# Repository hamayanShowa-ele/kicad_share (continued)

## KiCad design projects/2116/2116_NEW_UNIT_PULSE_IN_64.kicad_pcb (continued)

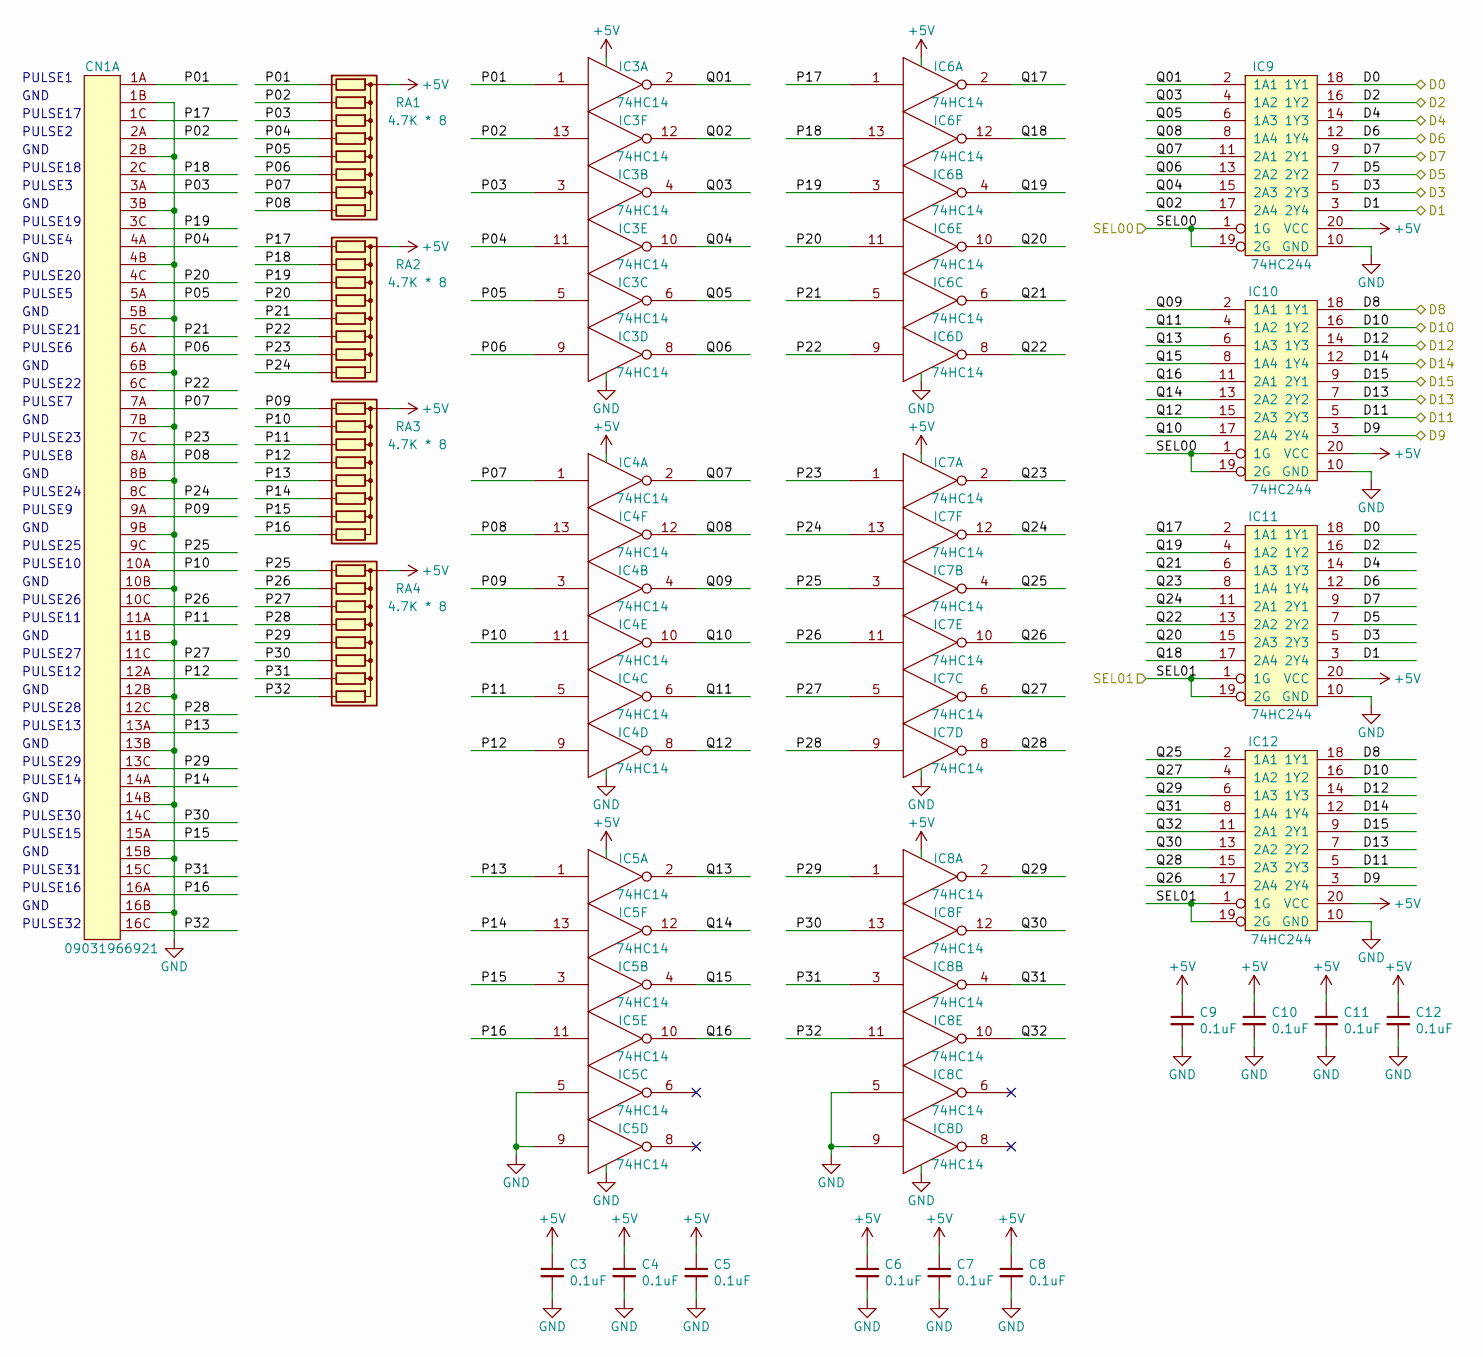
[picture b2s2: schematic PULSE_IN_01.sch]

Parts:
C3, C4, C5, C6, C7, C8, C9, C10, C11, C12: 0.1uF; C_0603
CN1: 09031966921; cn_09031966921
IC3, IC4, IC5, IC6, IC7, IC8: 74HC14; IC_DIP-14_W7.62mm
IC9, IC10, IC11, IC12: 74HC244; ic_DIP-20_W7.62mm
RA1, RA2, RA3, RA4: 4.7K * 8; RKC1_8B8

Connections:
+5V: C3.1, C4.1, C5.1, C6.1, C7.1, C8.1, C9.1, C10.1, C11.1, C12.1, IC3.14 (+5V), IC4.14 (+5V), IC5.14 (+5V), IC6.14 (+5V), IC7.14 (+5V), IC8.14 (+5V), IC9.20 (VCC), IC10.20 (VCC), IC11.20 (VCC), IC12.20 (VCC), RA1.1 (common), RA2.1 (common), RA3.1 (common), RA4.1 (common); also elsewhere on the board
/D0: IC9.18 (1Y1), IC11.18 (1Y1); also elsewhere on the board
/D1: IC9.3 (2Y4), IC11.3 (2Y4); also elsewhere on the board
/D2: IC9.16 (1Y2), IC11.16 (1Y2); also elsewhere on the board
/D3: IC9.5 (2Y3), IC11.5 (2Y3); also elsewhere on the board
/D4: IC9.14 (1Y3), IC11.14 (1Y3); also elsewhere on the board
/D5: IC9.7 (2Y2), IC11.7 (2Y2); also elsewhere on the board
/D6: IC9.12 (1Y4), IC11.12 (1Y4); also elsewhere on the board
/D7: IC9.9 (2Y1), IC11.9 (2Y1); also elsewhere on the board
/D8: IC10.18 (1Y1), IC12.18 (1Y1); also elsewhere on the board
/D9: IC10.3 (2Y4), IC12.3 (2Y4); also elsewhere on the board
/D10: IC10.16 (1Y2), IC12.16 (1Y2); also elsewhere on the board
/D11: IC10.5 (2Y3), IC12.5 (2Y3); also elsewhere on the board
/D12: IC10.14 (1Y3), IC12.14 (1Y3); also elsewhere on the board
/D13: IC10.7 (2Y2), IC12.7 (2Y2); also elsewhere on the board
/D14: IC10.12 (1Y4), IC12.12 (1Y4); also elsewhere on the board
/D15: IC10.9 (2Y1), IC12.9 (2Y1); also elsewhere on the board
/PULSE_IN_01/P01: CN1.1A, IC3.1, RA1.2 (R1)
/PULSE_IN_01/P02: CN1.2A, IC3.13, RA1.3 (R2)
/PULSE_IN_01/P03: CN1.3A, IC3.3, RA1.4 (R3)
/PULSE_IN_01/P04: CN1.4A, IC3.11, RA1.5 (R4)
/PULSE_IN_01/P05: CN1.5A, IC3.5, RA1.6 (R5)
/PULSE_IN_01/P06: CN1.6A, IC3.9, RA1.7 (R6)
/PULSE_IN_01/P07: CN1.7A, IC4.1, RA1.8 (R7)
/PULSE_IN_01/P08: CN1.8A, IC4.13, RA1.9 (R8)
/PULSE_IN_01/P09: CN1.9A, IC4.3, RA3.2 (R1)
/PULSE_IN_01/P10: CN1.10A, IC4.11, RA3.3 (R2)
/PULSE_IN_01/P11: CN1.11A, IC4.5, RA3.4 (R3)
/PULSE_IN_01/P12: CN1.12A, IC4.9, RA3.5 (R4)
/PULSE_IN_01/P13: CN1.13A, IC5.1, RA3.6 (R5)
/PULSE_IN_01/P14: CN1.14A, IC5.13, RA3.7 (R6)
/PULSE_IN_01/P15: CN1.15A, IC5.3, RA3.8 (R7)
/PULSE_IN_01/P16: CN1.16A, IC5.11, RA3.9 (R8)
/PULSE_IN_01/P17: CN1.1C, IC6.1, RA2.2 (R1)
/PULSE_IN_01/P18: CN1.2C, IC6.13, RA2.3 (R2)
/PULSE_IN_01/P19: CN1.3C, IC6.3, RA2.4 (R3)
/PULSE_IN_01/P20: CN1.4C, IC6.11, RA2.5 (R4)
/PULSE_IN_01/P21: CN1.5C, IC6.5, RA2.6 (R5)
/PULSE_IN_01/P22: CN1.6C, IC6.9, RA2.7 (R6)
/PULSE_IN_01/P23: CN1.7C, IC7.1, RA2.8 (R7)
/PULSE_IN_01/P24: CN1.8C, IC7.13, RA2.9 (R8)
/PULSE_IN_01/P25: CN1.9C, IC7.3, RA4.2 (R1)
/PULSE_IN_01/P26: CN1.10C, IC7.11, RA4.3 (R2)
/PULSE_IN_01/P27: CN1.11C, IC7.5, RA4.4 (R3)
/PULSE_IN_01/P28: CN1.12C, IC7.9, RA4.5 (R4)
/PULSE_IN_01/P29: CN1.13C, IC8.1, RA4.6 (R5)
/PULSE_IN_01/P30: CN1.14C, IC8.13, RA4.7 (R6)
/PULSE_IN_01/P31: CN1.15C, IC8.3, RA4.8 (R7)
/PULSE_IN_01/P32: CN1.16C, IC8.11, RA4.9 (R8)
/PULSE_IN_01/Q01: IC3.2, IC9.2 (1A1)
/PULSE_IN_01/Q02: IC3.12, IC9.17 (2A4)
/PULSE_IN_01/Q03: IC3.4, IC9.4 (1A2)
/PULSE_IN_01/Q04: IC3.10, IC9.15 (2A3)
/PULSE_IN_01/Q05: IC3.6, IC9.6 (1A3)
/PULSE_IN_01/Q06: IC3.8, IC9.13 (2A2)
/PULSE_IN_01/Q07: IC4.2, IC9.11 (2A1)
/PULSE_IN_01/Q08: IC4.12, IC9.8 (1A4)
/PULSE_IN_01/Q09: IC4.4, IC10.2 (1A1)
/PULSE_IN_01/Q10: IC4.10, IC10.17 (2A4)
/PULSE_IN_01/Q11: IC4.6, IC10.4 (1A2)
/PULSE_IN_01/Q12: IC4.8, IC10.15 (2A3)
/PULSE_IN_01/Q13: IC5.2, IC10.6 (1A3)
/PULSE_IN_01/Q14: IC5.12, IC10.13 (2A2)
/PULSE_IN_01/Q15: IC5.4, IC10.8 (1A4)
/PULSE_IN_01/Q16: IC5.10, IC10.11 (2A1)
/PULSE_IN_01/Q17: IC6.2, IC11.2 (1A1)
/PULSE_IN_01/Q18: IC6.12, IC11.17 (2A4)
/PULSE_IN_01/Q19: IC6.4, IC11.4 (1A2)
/PULSE_IN_01/Q20: IC6.10, IC11.15 (2A3)
/PULSE_IN_01/Q21: IC6.6, IC11.6 (1A3)
/PULSE_IN_01/Q22: IC6.8, IC11.13 (2A2)
/PULSE_IN_01/Q23: IC7.2, IC11.8 (1A4)
/PULSE_IN_01/Q24: IC7.12, IC11.11 (2A1)
/PULSE_IN_01/Q25: IC7.4, IC12.2 (1A1)
/PULSE_IN_01/Q26: IC7.10, IC12.17 (2A4)
/PULSE_IN_01/Q27: IC7.6, IC12.4 (1A2)
/PULSE_IN_01/Q28: IC7.8, IC12.15 (2A3)
/PULSE_IN_01/Q29: IC8.2, IC12.6 (1A3)
/PULSE_IN_01/Q30: IC8.12, IC12.13 (2A2)
/PULSE_IN_01/Q31: IC8.4, IC12.8 (1A4)
/PULSE_IN_01/Q32: IC8.10, IC12.11 (2A1)
/SEL00: IC9.1 (1G), IC9.19 (2G), IC10.1 (1G), IC10.19 (2G); also elsewhere on the board
/SEL01: IC11.1 (1G), IC11.19 (2G), IC12.1 (1G), IC12.19 (2G); also elsewhere on the board
GND: C3.2, C4.2, C5.2, C6.2, C7.2, C8.2, C9.2, C10.2, C11.2, C12.2, CN1.1B, CN1.2B, CN1.3B, CN1.4B, CN1.5B, CN1.6B, CN1.7B, CN1.8B, CN1.9B, CN1.10B, CN1.11B, CN1.12B, CN1.13B, CN1.14B, CN1.15B, CN1.16B, IC3.7 (GND), IC4.7 (GND), IC5.5, IC5.7 (GND), IC5.9, IC6.7 (GND), IC7.7 (GND), IC8.5, IC8.7 (GND), IC8.9, IC9.10 (GND), IC10.10 (GND), IC11.10 (GND), IC12.10 (GND); also elsewhere on the board

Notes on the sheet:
GND
PULSE1
PULSE2
PULSE3
PULSE4
PULSE5
PULSE6
PULSE7
PULSE8
PULSE9
PULSE10
PULSE11
PULSE12
PULSE13
PULSE14
PULSE15
PULSE16
PULSE32
PULSE17
PULSE18
PULSE19
PULSE20
PULSE21
PULSE22
PULSE23
PULSE24
PULSE25
PULSE26
PULSE27
PULSE28
PULSE29
PULSE30
PULSE31

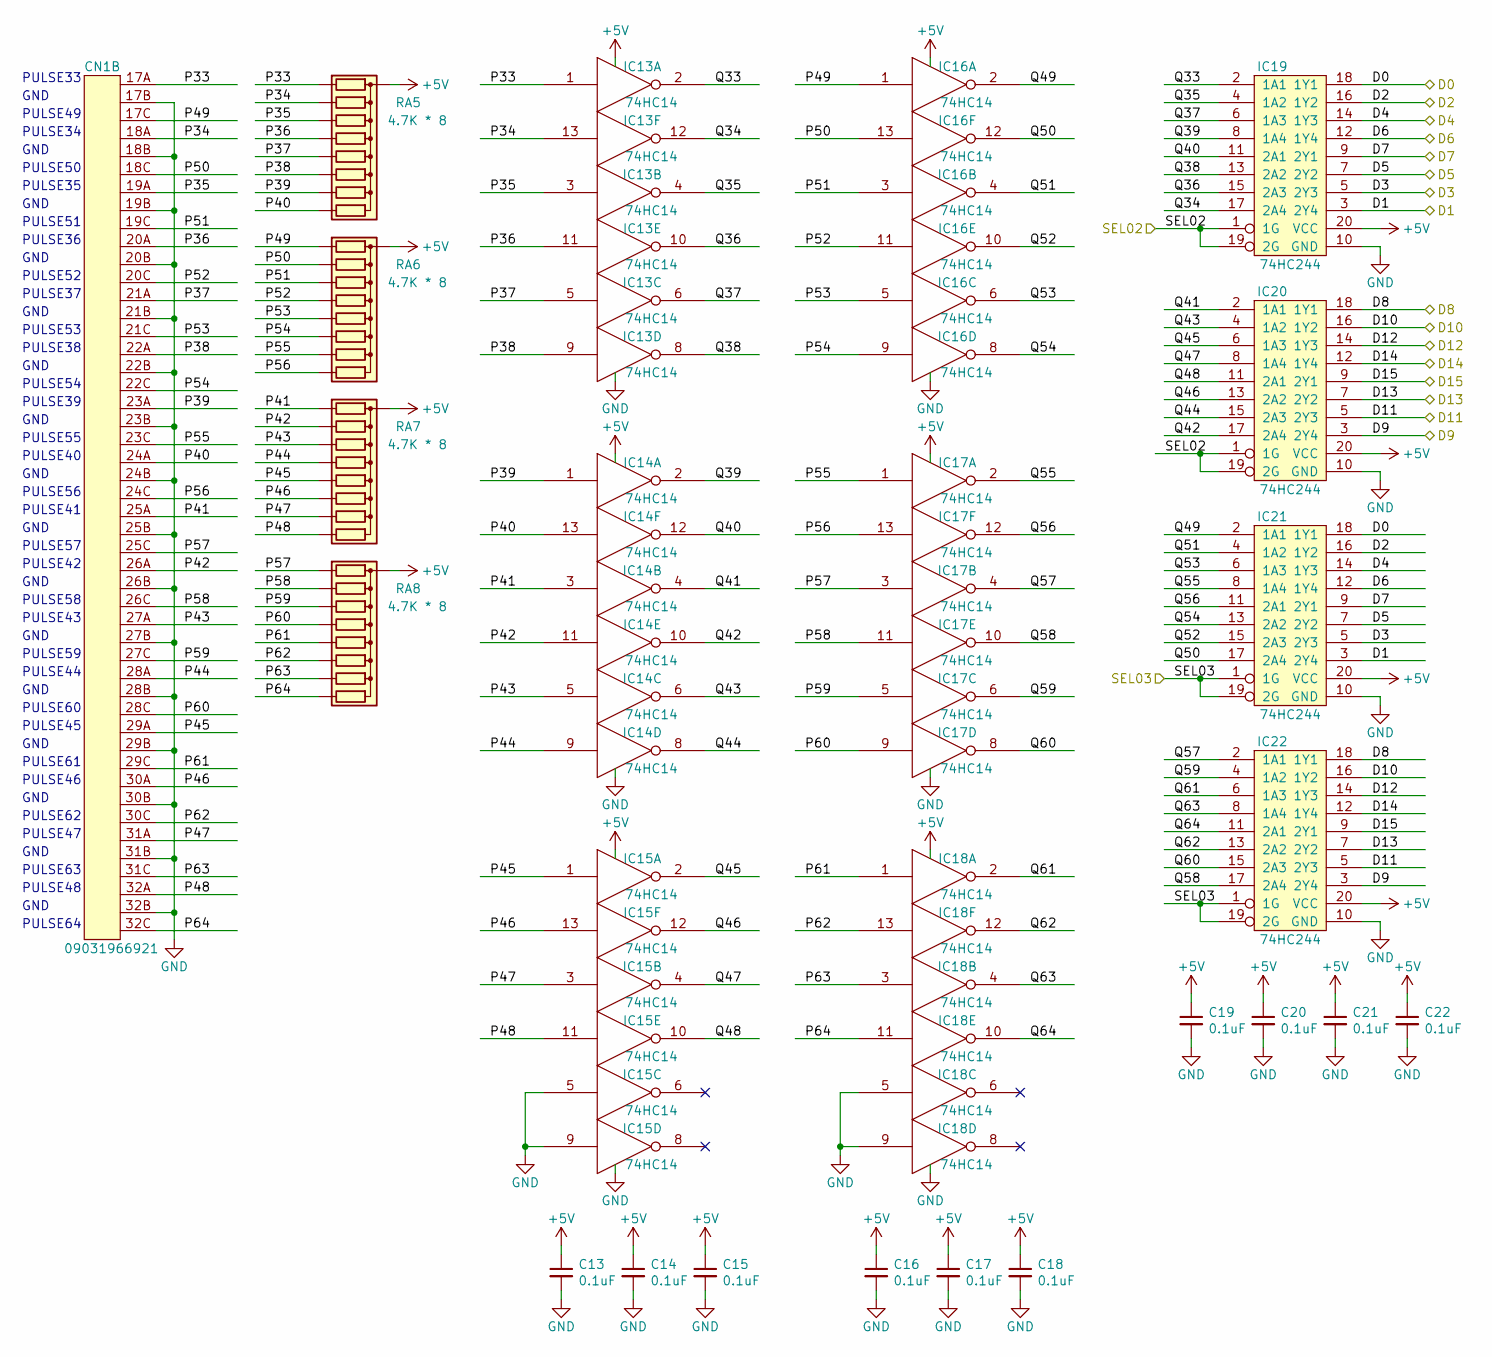
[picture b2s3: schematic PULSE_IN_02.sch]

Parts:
C13, C14, C15, C16, C17, C18, C19, C20, C21, C22: 0.1uF; C_0603
CN1: 09031966921; cn_09031966921
IC13, IC14, IC15, IC16, IC17, IC18: 74HC14; IC_DIP-14_W7.62mm
IC19, IC20, IC21, IC22: 74HC244; ic_DIP-20_W7.62mm
RA5, RA6, RA7, RA8: 4.7K * 8; RKC1_8B8

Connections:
+5V: C13.1, C14.1, C15.1, C16.1, C17.1, C18.1, C19.1, C20.1, C21.1, C22.1, IC13.14 (+5V), IC14.14 (+5V), IC15.14 (+5V), IC16.14 (+5V), IC17.14 (+5V), IC18.14 (+5V), IC19.20 (VCC), IC20.20 (VCC), IC21.20 (VCC), IC22.20 (VCC), RA5.1 (common), RA6.1 (common), RA7.1 (common), RA8.1 (common); also elsewhere on the board
/D0: IC19.18 (1Y1), IC21.18 (1Y1); also elsewhere on the board
/D1: IC19.3 (2Y4), IC21.3 (2Y4); also elsewhere on the board
/D2: IC19.16 (1Y2), IC21.16 (1Y2); also elsewhere on the board
/D3: IC19.5 (2Y3), IC21.5 (2Y3); also elsewhere on the board
/D4: IC19.14 (1Y3), IC21.14 (1Y3); also elsewhere on the board
/D5: IC19.7 (2Y2), IC21.7 (2Y2); also elsewhere on the board
/D6: IC19.12 (1Y4), IC21.12 (1Y4); also elsewhere on the board
/D7: IC19.9 (2Y1), IC21.9 (2Y1); also elsewhere on the board
/D8: IC20.18 (1Y1), IC22.18 (1Y1); also elsewhere on the board
/D9: IC20.3 (2Y4), IC22.3 (2Y4); also elsewhere on the board
/D10: IC20.16 (1Y2), IC22.16 (1Y2); also elsewhere on the board
/D11: IC20.5 (2Y3), IC22.5 (2Y3); also elsewhere on the board
/D12: IC20.14 (1Y3), IC22.14 (1Y3); also elsewhere on the board
/D13: IC20.7 (2Y2), IC22.7 (2Y2); also elsewhere on the board
/D14: IC20.12 (1Y4), IC22.12 (1Y4); also elsewhere on the board
/D15: IC20.9 (2Y1), IC22.9 (2Y1); also elsewhere on the board
/PULSE_IN_02/P33: CN1.17A, IC13.1, RA5.2 (R1)
/PULSE_IN_02/P34: CN1.18A, IC13.13, RA5.3 (R2)
/PULSE_IN_02/P35: CN1.19A, IC13.3, RA5.4 (R3)
/PULSE_IN_02/P36: CN1.20A, IC13.11, RA5.5 (R4)
/PULSE_IN_02/P37: CN1.21A, IC13.5, RA5.6 (R5)
/PULSE_IN_02/P38: CN1.22A, IC13.9, RA5.7 (R6)
/PULSE_IN_02/P39: CN1.23A, IC14.1, RA5.8 (R7)
/PULSE_IN_02/P40: CN1.24A, IC14.13, RA5.9 (R8)
/PULSE_IN_02/P41: CN1.25A, IC14.3, RA7.2 (R1)
/PULSE_IN_02/P42: CN1.26A, IC14.11, RA7.3 (R2)
/PULSE_IN_02/P43: CN1.27A, IC14.5, RA7.4 (R3)
/PULSE_IN_02/P44: CN1.28A, IC14.9, RA7.5 (R4)
/PULSE_IN_02/P45: CN1.29A, IC15.1, RA7.6 (R5)
/PULSE_IN_02/P46: CN1.30A, IC15.13, RA7.7 (R6)
/PULSE_IN_02/P47: CN1.31A, IC15.3, RA7.8 (R7)
/PULSE_IN_02/P48: CN1.32A, IC15.11, RA7.9 (R8)
/PULSE_IN_02/P49: CN1.17C, IC16.1, RA6.2 (R1)
/PULSE_IN_02/P50: CN1.18C, IC16.13, RA6.3 (R2)
/PULSE_IN_02/P51: CN1.19C, IC16.3, RA6.4 (R3)
/PULSE_IN_02/P52: CN1.20C, IC16.11, RA6.5 (R4)
/PULSE_IN_02/P53: CN1.21C, IC16.5, RA6.6 (R5)
/PULSE_IN_02/P54: CN1.22C, IC16.9, RA6.7 (R6)
/PULSE_IN_02/P55: CN1.23C, IC17.1, RA6.8 (R7)
/PULSE_IN_02/P56: CN1.24C, IC17.13, RA6.9 (R8)
/PULSE_IN_02/P57: CN1.25C, IC17.3, RA8.2 (R1)
/PULSE_IN_02/P58: CN1.26C, IC17.11, RA8.3 (R2)
/PULSE_IN_02/P59: CN1.27C, IC17.5, RA8.4 (R3)
/PULSE_IN_02/P60: CN1.28C, IC17.9, RA8.5 (R4)
/PULSE_IN_02/P61: CN1.29C, IC18.1, RA8.6 (R5)
/PULSE_IN_02/P62: CN1.30C, IC18.13, RA8.7 (R6)
/PULSE_IN_02/P63: CN1.31C, IC18.3, RA8.8 (R7)
/PULSE_IN_02/P64: CN1.32C, IC18.11, RA8.9 (R8)
/PULSE_IN_02/Q33: IC13.2, IC19.2 (1A1)
/PULSE_IN_02/Q34: IC13.12, IC19.17 (2A4)
/PULSE_IN_02/Q35: IC13.4, IC19.4 (1A2)
/PULSE_IN_02/Q36: IC13.10, IC19.15 (2A3)
/PULSE_IN_02/Q37: IC13.6, IC19.6 (1A3)
/PULSE_IN_02/Q38: IC13.8, IC19.13 (2A2)
/PULSE_IN_02/Q39: IC14.2, IC19.8 (1A4)
/PULSE_IN_02/Q40: IC14.12, IC19.11 (2A1)
/PULSE_IN_02/Q41: IC14.4, IC20.2 (1A1)
/PULSE_IN_02/Q42: IC14.10, IC20.17 (2A4)
/PULSE_IN_02/Q43: IC14.6, IC20.4 (1A2)
/PULSE_IN_02/Q44: IC14.8, IC20.15 (2A3)
/PULSE_IN_02/Q45: IC15.2, IC20.6 (1A3)
/PULSE_IN_02/Q46: IC15.12, IC20.13 (2A2)
/PULSE_IN_02/Q47: IC15.4, IC20.8 (1A4)
/PULSE_IN_02/Q48: IC15.10, IC20.11 (2A1)
/PULSE_IN_02/Q49: IC16.2, IC21.2 (1A1)
/PULSE_IN_02/Q50: IC16.12, IC21.17 (2A4)
/PULSE_IN_02/Q51: IC16.4, IC21.4 (1A2)
/PULSE_IN_02/Q52: IC16.10, IC21.15 (2A3)
/PULSE_IN_02/Q53: IC16.6, IC21.6 (1A3)
/PULSE_IN_02/Q54: IC16.8, IC21.13 (2A2)
/PULSE_IN_02/Q55: IC17.2, IC21.8 (1A4)
/PULSE_IN_02/Q56: IC17.12, IC21.11 (2A1)
/PULSE_IN_02/Q57: IC17.4, IC22.2 (1A1)
/PULSE_IN_02/Q58: IC17.10, IC22.17 (2A4)
/PULSE_IN_02/Q59: IC17.6, IC22.4 (1A2)
/PULSE_IN_02/Q60: IC17.8, IC22.15 (2A3)
/PULSE_IN_02/Q61: IC18.2, IC22.6 (1A3)
/PULSE_IN_02/Q62: IC18.12, IC22.13 (2A2)
/PULSE_IN_02/Q63: IC18.4, IC22.8 (1A4)
/PULSE_IN_02/Q64: IC18.10, IC22.11 (2A1)
/SEL02: IC19.1 (1G), IC19.19 (2G), IC20.1 (1G), IC20.19 (2G); also elsewhere on the board
/SEL03: IC21.1 (1G), IC21.19 (2G), IC22.1 (1G), IC22.19 (2G); also elsewhere on the board
GND: C13.2, C14.2, C15.2, C16.2, C17.2, C18.2, C19.2, C20.2, C21.2, C22.2, CN1.17B, CN1.18B, CN1.19B, CN1.20B, CN1.21B, CN1.22B, CN1.23B, CN1.24B, CN1.25B, CN1.26B, CN1.27B, CN1.28B, CN1.29B, CN1.30B, CN1.31B, CN1.32B, IC13.7 (GND), IC14.7 (GND), IC15.5, IC15.7 (GND), IC15.9, IC16.7 (GND), IC17.7 (GND), IC18.5, IC18.7 (GND), IC18.9, IC19.10 (GND), IC20.10 (GND), IC21.10 (GND), IC22.10 (GND); also elsewhere on the board

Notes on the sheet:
PULSE33
PULSE34
PULSE36
PULSE37
PULSE38
PULSE39
PULSE40
PULSE41
PULSE42
PULSE43
PULSE44
PULSE45
PULSE46
PULSE47
PULSE48
GND
PULSE64
PULSE49
PULSE50
PULSE51
PULSE52
PULSE53
PULSE54
PULSE55
PULSE56
PULSE57
PULSE58
PULSE59
PULSE60
PULSE61
PULSE62
PULSE63
PULSE35

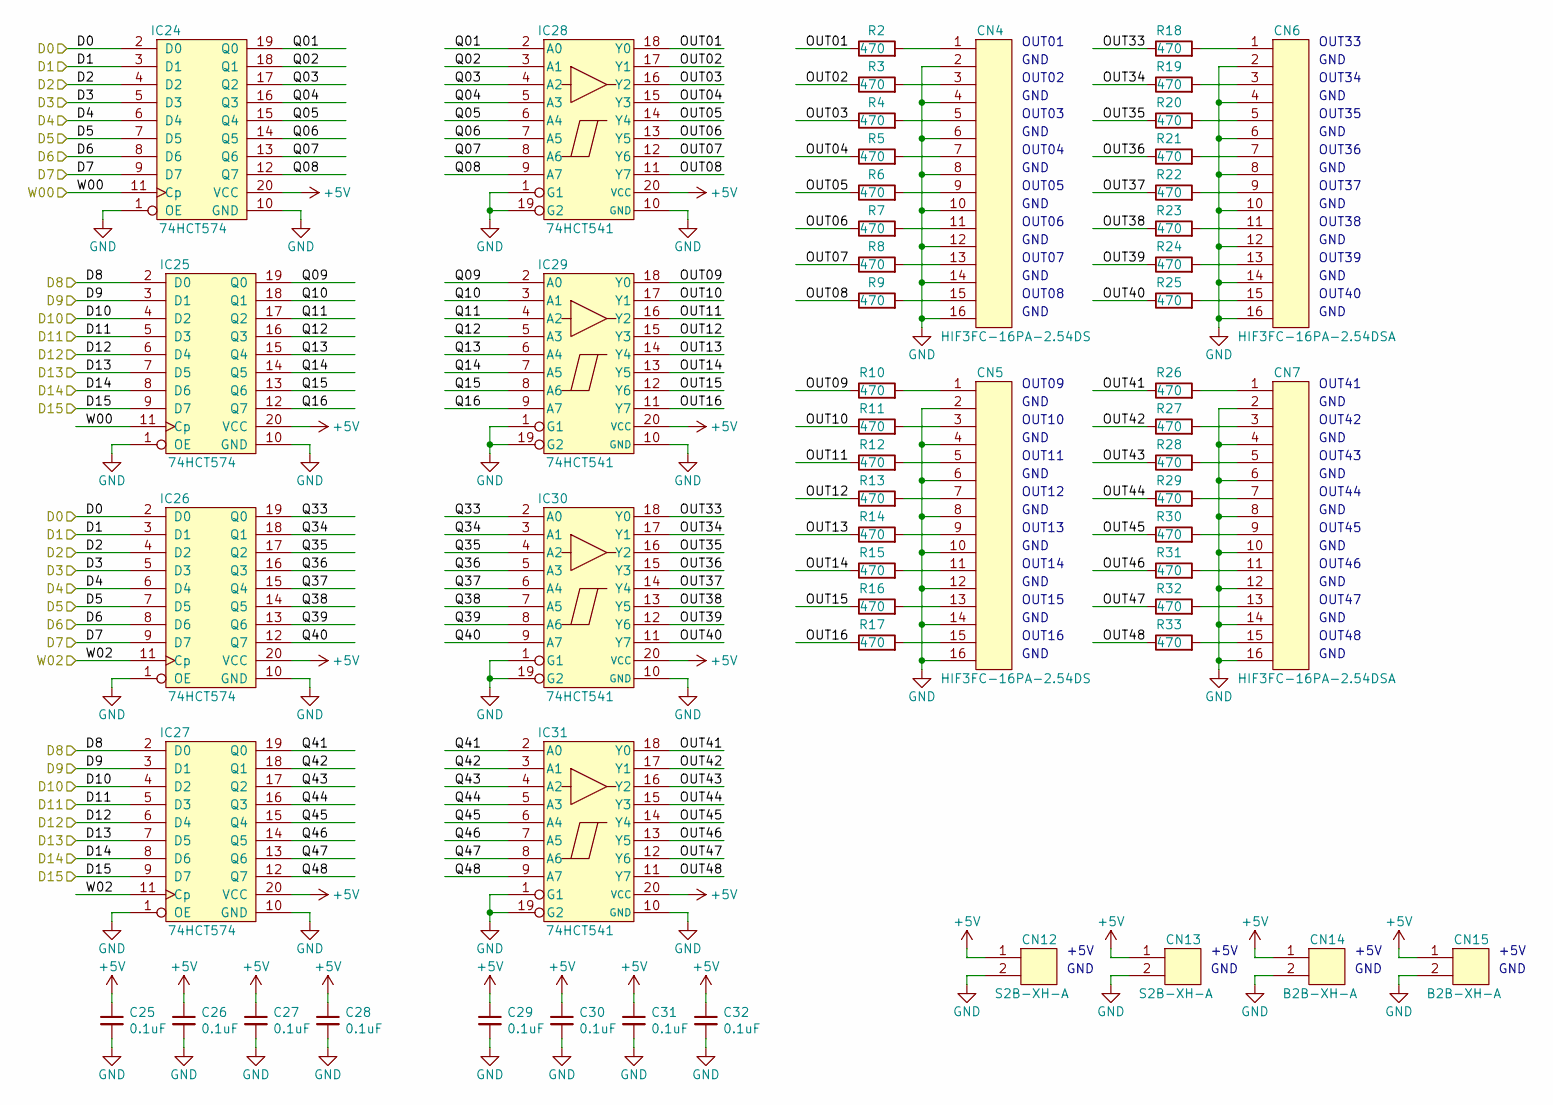
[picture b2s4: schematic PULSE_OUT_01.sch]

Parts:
C25, C26, C27, C28, C29, C30, C31, C32: 0.1uF; C_0603
CN4, CN5: HIF3FC-16PA-2.54DS; cn_HIF3FC-16PA-254DS
CN6, CN7: HIF3FC-16PA-2.54DSA; cn_HIF3FC-16PA-254DSA
CN12, CN13: S2B-XH-A
CN14, CN15: B2B-XH-A; cn_B2B-XH-A
IC24, IC25, IC26, IC27: 74HCT574; ic_DIP-20_W7.62mm
IC28, IC29, IC30, IC31: 74HCT541; ic_DIP-20_W7.62mm
R2, R3, R4, R5, R6, R7, R8, R9, R10, R11, R12, R13, R14, R15, R16, R17, R18, R19, R20, R21, R22, R23, R24, R25, R26, R27, R28, R29, R30, R31, R32, R33: 470; C_0603

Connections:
+5V: C25.1, C26.1, C27.1, C28.1, C29.1, C30.1, C31.1, C32.1, CN12.1, CN13.1, CN14.1, CN15.1, IC24.20 (VCC), IC25.20 (VCC), IC26.20 (VCC), IC27.20 (VCC), IC28.20 (VCC), IC29.20 (VCC), IC30.20 (VCC), IC31.20 (VCC); also elsewhere on the board
/D0: IC24.2 (D0), IC26.2 (D0); also elsewhere on the board
/D1: IC24.3 (D1), IC26.3 (D1); also elsewhere on the board
/D2: IC24.4 (D2), IC26.4 (D2); also elsewhere on the board
/D3: IC24.5 (D3), IC26.5 (D3); also elsewhere on the board
/D4: IC24.6 (D4), IC26.6 (D4); also elsewhere on the board
/D5: IC24.7 (D5), IC26.7 (D5); also elsewhere on the board
/D6: IC24.8 (D6), IC26.8 (D6); also elsewhere on the board
/D7: IC24.9 (D7), IC26.9 (D7); also elsewhere on the board
/D8: IC25.2 (D0), IC27.2 (D0); also elsewhere on the board
/D9: IC25.3 (D1), IC27.3 (D1); also elsewhere on the board
/D10: IC25.4 (D2), IC27.4 (D2); also elsewhere on the board
/D11: IC25.5 (D3), IC27.5 (D3); also elsewhere on the board
/D12: IC25.6 (D4), IC27.6 (D4); also elsewhere on the board
/D13: IC25.7 (D5), IC27.7 (D5); also elsewhere on the board
/D14: IC25.8 (D6), IC27.8 (D6); also elsewhere on the board
/D15: IC25.9 (D7), IC27.9 (D7); also elsewhere on the board
/PULSE_OUT_01/OUT01: IC28.18 (Y0), R2.1
/PULSE_OUT_01/OUT02: IC28.17 (Y1), R3.1
/PULSE_OUT_01/OUT03: IC28.16 (Y2), R4.1
/PULSE_OUT_01/OUT04: IC28.15 (Y3), R5.1
/PULSE_OUT_01/OUT05: IC28.14 (Y4), R6.1
/PULSE_OUT_01/OUT06: IC28.13 (Y5), R7.1
/PULSE_OUT_01/OUT07: IC28.12 (Y6), R8.1
/PULSE_OUT_01/OUT08: IC28.11 (Y7), R9.1
/PULSE_OUT_01/OUT09: IC29.18 (Y0), R10.1
/PULSE_OUT_01/OUT10: IC29.17 (Y1), R11.1
/PULSE_OUT_01/OUT11: IC29.16 (Y2), R12.1
/PULSE_OUT_01/OUT12: IC29.15 (Y3), R13.1
/PULSE_OUT_01/OUT13: IC29.14 (Y4), R14.1
/PULSE_OUT_01/OUT14: IC29.13 (Y5), R15.1
/PULSE_OUT_01/OUT15: IC29.12 (Y6), R16.1
/PULSE_OUT_01/OUT16: IC29.11 (Y7), R17.1
/PULSE_OUT_01/OUT33: IC30.18 (Y0), R18.1
/PULSE_OUT_01/OUT34: IC30.17 (Y1), R19.1
/PULSE_OUT_01/OUT35: IC30.16 (Y2), R20.1
/PULSE_OUT_01/OUT36: IC30.15 (Y3), R21.1
/PULSE_OUT_01/OUT37: IC30.14 (Y4), R22.1
/PULSE_OUT_01/OUT38: IC30.13 (Y5), R23.1
/PULSE_OUT_01/OUT39: IC30.12 (Y6), R24.1
/PULSE_OUT_01/OUT40: IC30.11 (Y7), R25.1
/PULSE_OUT_01/OUT41: IC31.18 (Y0), R26.1
/PULSE_OUT_01/OUT42: IC31.17 (Y1), R27.1
/PULSE_OUT_01/OUT43: IC31.16 (Y2), R28.1
/PULSE_OUT_01/OUT44: IC31.15 (Y3), R29.1
/PULSE_OUT_01/OUT45: IC31.14 (Y4), R30.1
/PULSE_OUT_01/OUT46: IC31.13 (Y5), R31.1
/PULSE_OUT_01/OUT47: IC31.12 (Y6), R32.1
/PULSE_OUT_01/OUT48: IC31.11 (Y7), R33.1
/PULSE_OUT_01/Q01: IC24.19 (Q0), IC28.2 (A0)
/PULSE_OUT_01/Q02: IC24.18 (Q1), IC28.3 (A1)
/PULSE_OUT_01/Q03: IC24.17 (Q2), IC28.4 (A2)
/PULSE_OUT_01/Q04: IC24.16 (Q3), IC28.5 (A3)
/PULSE_OUT_01/Q05: IC24.15 (Q4), IC28.6 (A4)
/PULSE_OUT_01/Q06: IC24.14 (Q5), IC28.7 (A5)
/PULSE_OUT_01/Q07: IC24.13 (Q6), IC28.8 (A6)
/PULSE_OUT_01/Q08: IC24.12 (Q7), IC28.9 (A7)
/PULSE_OUT_01/Q09: IC25.19 (Q0), IC29.2 (A0)
/PULSE_OUT_01/Q10: IC25.18 (Q1), IC29.3 (A1)
/PULSE_OUT_01/Q11: IC25.17 (Q2), IC29.4 (A2)
/PULSE_OUT_01/Q12: IC25.16 (Q3), IC29.5 (A3)
/PULSE_OUT_01/Q13: IC25.15 (Q4), IC29.6 (A4)
/PULSE_OUT_01/Q14: IC25.14 (Q5), IC29.7 (A5)
/PULSE_OUT_01/Q15: IC25.13 (Q6), IC29.8 (A6)
/PULSE_OUT_01/Q16: IC25.12 (Q7), IC29.9 (A7)
/PULSE_OUT_01/Q33: IC26.19 (Q0), IC30.2 (A0)
/PULSE_OUT_01/Q34: IC26.18 (Q1), IC30.3 (A1)
/PULSE_OUT_01/Q35: IC26.17 (Q2), IC30.4 (A2)
/PULSE_OUT_01/Q36: IC26.16 (Q3), IC30.5 (A3)
/PULSE_OUT_01/Q37: IC26.15 (Q4), IC30.6 (A4)
/PULSE_OUT_01/Q38: IC26.14 (Q5), IC30.7 (A5)
/PULSE_OUT_01/Q39: IC26.13 (Q6), IC30.8 (A6)
/PULSE_OUT_01/Q40: IC26.12 (Q7), IC30.9 (A7)
/PULSE_OUT_01/Q41: IC27.19 (Q0), IC31.2 (A0)
/PULSE_OUT_01/Q42: IC27.18 (Q1), IC31.3 (A1)
/PULSE_OUT_01/Q43: IC27.17 (Q2), IC31.4 (A2)
/PULSE_OUT_01/Q44: IC27.16 (Q3), IC31.5 (A3)
/PULSE_OUT_01/Q45: IC27.15 (Q4), IC31.6 (A4)
/PULSE_OUT_01/Q46: IC27.14 (Q5), IC31.7 (A5)
/PULSE_OUT_01/Q47: IC27.13 (Q6), IC31.8 (A6)
/PULSE_OUT_01/Q48: IC27.12 (Q7), IC31.9 (A7)
/W00: IC24.11 (Cp), IC25.11 (Cp); also elsewhere on the board
/W02: IC26.11 (Cp), IC27.11 (Cp); also elsewhere on the board
GND: C25.2, C26.2, C27.2, C28.2, C29.2, C30.2, C31.2, C32.2, CN4.2, CN4.4, CN4.6, CN4.8, CN4.10, CN4.12, CN4.14, CN4.16, CN5.2, CN5.4, CN5.6, CN5.8, CN5.10, CN5.12, CN5.14, CN5.16, CN6.2, CN6.4, CN6.6, CN6.8, CN6.10, CN6.12, CN6.14, CN6.16, CN7.2, CN7.4, CN7.6, CN7.8, CN7.10, CN7.12, CN7.14, CN7.16, CN12.2, CN13.2, CN14.2, CN15.2, IC24.1 (OE), IC24.10 (GND), IC25.1 (OE), IC25.10 (GND), IC26.1 (OE), IC26.10 (GND), IC27.1 (OE), IC27.10 (GND), IC28.1 (G1), IC28.10 (GND), IC28.19 (G2), IC29.1 (G1), IC29.10 (GND), IC29.19 (G2), IC30.1 (G1), IC30.10 (GND), IC30.19 (G2), IC31.1 (G1), IC31.10 (GND), IC31.19 (G2); also elsewhere on the board
unnamed: CN4.1, R2.2
unnamed: CN4.3, R3.2
unnamed: CN4.5, R4.2
unnamed: CN4.7, R5.2
unnamed: CN4.9, R6.2
unnamed: CN4.11, R7.2
unnamed: CN4.13, R8.2
unnamed: CN4.15, R9.2
unnamed: CN5.1, R10.2
unnamed: CN5.3, R11.2
unnamed: CN5.5, R12.2
unnamed: CN5.7, R13.2
unnamed: CN5.9, R14.2
unnamed: CN5.11, R15.2
unnamed: CN5.13, R16.2
unnamed: CN5.15, R17.2
unnamed: CN6.1, R18.2
unnamed: CN6.3, R19.2
unnamed: CN6.5, R20.2
unnamed: CN6.7, R21.2
unnamed: CN6.9, R22.2
unnamed: CN6.11, R23.2
unnamed: CN6.13, R24.2
unnamed: CN6.15, R25.2
unnamed: CN7.1, R26.2
unnamed: CN7.3, R27.2
unnamed: CN7.5, R28.2
unnamed: CN7.7, R29.2
unnamed: CN7.9, R30.2
unnamed: CN7.11, R31.2
unnamed: CN7.13, R32.2
unnamed: CN7.15, R33.2

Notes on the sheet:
OUT33
GND
OUT34
OUT35
OUT36
OUT37
OUT38
OUT39
OUT40
OUT41
OUT42
OUT43
OUT44
OUT45
OUT46
OUT47
OUT48
OUT01
OUT02
OUT03
OUT04
OUT05
OUT06
OUT07
OUT08
OUT09
OUT10
OUT11
OUT12
OUT13
OUT14
OUT15
OUT16
+5V

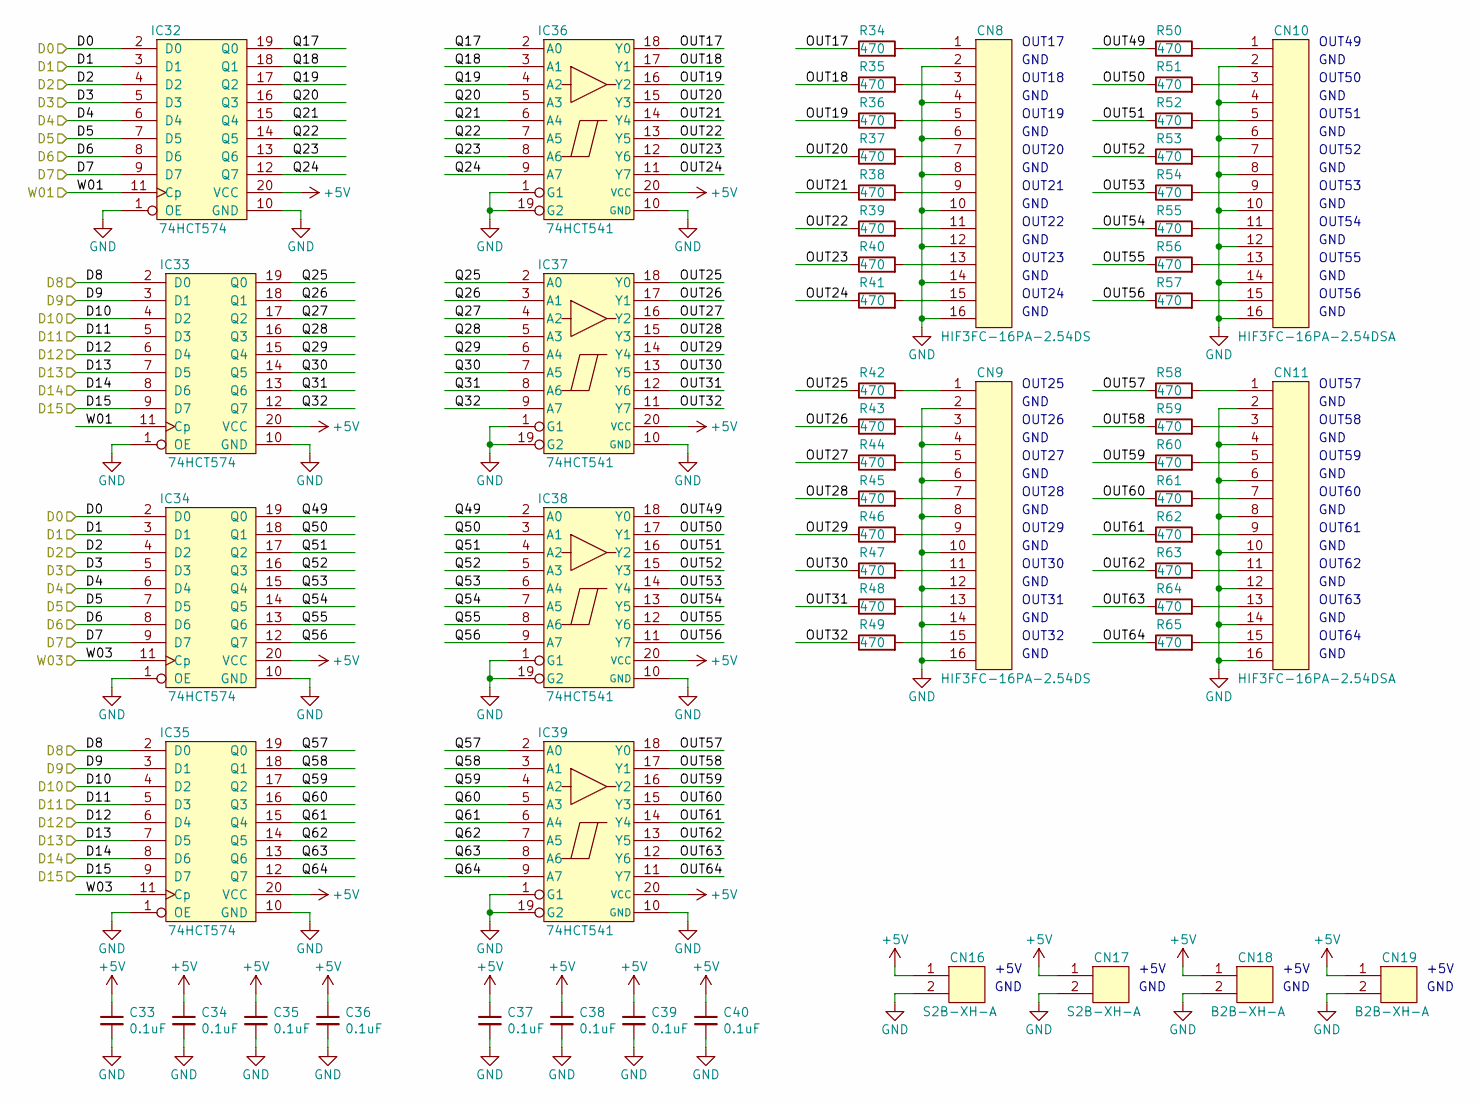
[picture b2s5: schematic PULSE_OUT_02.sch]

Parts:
C33, C34, C35, C36, C37, C38, C39, C40: 0.1uF; C_0603
CN8, CN9: HIF3FC-16PA-2.54DS; cn_HIF3FC-16PA-254DS
CN10, CN11: HIF3FC-16PA-2.54DSA; cn_HIF3FC-16PA-254DSA
CN16, CN17: S2B-XH-A
CN18, CN19: B2B-XH-A; cn_B2B-XH-A
IC32, IC33, IC34, IC35: 74HCT574; ic_DIP-20_W7.62mm
IC36, IC37, IC38, IC39: 74HCT541; ic_DIP-20_W7.62mm
R34, R35, R36, R37, R38, R39, R40, R41, R42, R43, R44, R45, R46, R47, R48, R49, R50, R51, R52, R53, R54, R55, R56, R57, R58, R59, R60, R61, R62, R63, R64, R65: 470; C_0603

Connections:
+5V: C33.1, C34.1, C35.1, C36.1, C37.1, C38.1, C39.1, C40.1, CN16.1, CN17.1, CN18.1, CN19.1, IC32.20 (VCC), IC33.20 (VCC), IC34.20 (VCC), IC35.20 (VCC), IC36.20 (VCC), IC37.20 (VCC), IC38.20 (VCC), IC39.20 (VCC); also elsewhere on the board
/D0: IC32.2 (D0), IC34.2 (D0); also elsewhere on the board
/D1: IC32.3 (D1), IC34.3 (D1); also elsewhere on the board
/D2: IC32.4 (D2), IC34.4 (D2); also elsewhere on the board
/D3: IC32.5 (D3), IC34.5 (D3); also elsewhere on the board
/D4: IC32.6 (D4), IC34.6 (D4); also elsewhere on the board
/D5: IC32.7 (D5), IC34.7 (D5); also elsewhere on the board
/D6: IC32.8 (D6), IC34.8 (D6); also elsewhere on the board
/D7: IC32.9 (D7), IC34.9 (D7); also elsewhere on the board
/D8: IC33.2 (D0), IC35.2 (D0); also elsewhere on the board
/D9: IC33.3 (D1), IC35.3 (D1); also elsewhere on the board
/D10: IC33.4 (D2), IC35.4 (D2); also elsewhere on the board
/D11: IC33.5 (D3), IC35.5 (D3); also elsewhere on the board
/D12: IC33.6 (D4), IC35.6 (D4); also elsewhere on the board
/D13: IC33.7 (D5), IC35.7 (D5); also elsewhere on the board
/D14: IC33.8 (D6), IC35.8 (D6); also elsewhere on the board
/D15: IC33.9 (D7), IC35.9 (D7); also elsewhere on the board
/PULSE_OUT_02/OUT17: IC36.18 (Y0), R34.1
/PULSE_OUT_02/OUT18: IC36.17 (Y1), R35.1
/PULSE_OUT_02/OUT19: IC36.16 (Y2), R36.1
/PULSE_OUT_02/OUT20: IC36.15 (Y3), R37.1
/PULSE_OUT_02/OUT21: IC36.14 (Y4), R38.1
/PULSE_OUT_02/OUT22: IC36.13 (Y5), R39.1
/PULSE_OUT_02/OUT23: IC36.12 (Y6), R40.1
/PULSE_OUT_02/OUT24: IC36.11 (Y7), R41.1
/PULSE_OUT_02/OUT25: IC37.18 (Y0), R42.1
/PULSE_OUT_02/OUT26: IC37.17 (Y1), R43.1
/PULSE_OUT_02/OUT27: IC37.16 (Y2), R44.1
/PULSE_OUT_02/OUT28: IC37.15 (Y3), R45.1
/PULSE_OUT_02/OUT29: IC37.14 (Y4), R46.1
/PULSE_OUT_02/OUT30: IC37.13 (Y5), R47.1
/PULSE_OUT_02/OUT31: IC37.12 (Y6), R48.1
/PULSE_OUT_02/OUT32: IC37.11 (Y7), R49.1
/PULSE_OUT_02/OUT49: IC38.18 (Y0), R50.1
/PULSE_OUT_02/OUT50: IC38.17 (Y1), R51.1
/PULSE_OUT_02/OUT51: IC38.16 (Y2), R52.1
/PULSE_OUT_02/OUT52: IC38.15 (Y3), R53.1
/PULSE_OUT_02/OUT53: IC38.14 (Y4), R54.1
/PULSE_OUT_02/OUT54: IC38.13 (Y5), R55.1
/PULSE_OUT_02/OUT55: IC38.12 (Y6), R56.1
/PULSE_OUT_02/OUT56: IC38.11 (Y7), R57.1
/PULSE_OUT_02/OUT57: IC39.18 (Y0), R58.1
/PULSE_OUT_02/OUT58: IC39.17 (Y1), R59.1
/PULSE_OUT_02/OUT59: IC39.16 (Y2), R60.1
/PULSE_OUT_02/OUT60: IC39.15 (Y3), R61.1
/PULSE_OUT_02/OUT61: IC39.14 (Y4), R62.1
/PULSE_OUT_02/OUT62: IC39.13 (Y5), R63.1
/PULSE_OUT_02/OUT63: IC39.12 (Y6), R64.1
/PULSE_OUT_02/OUT64: IC39.11 (Y7), R65.1
/PULSE_OUT_02/Q17: IC32.19 (Q0), IC36.2 (A0)
/PULSE_OUT_02/Q18: IC32.18 (Q1), IC36.3 (A1)
/PULSE_OUT_02/Q19: IC32.17 (Q2), IC36.4 (A2)
/PULSE_OUT_02/Q20: IC32.16 (Q3), IC36.5 (A3)
/PULSE_OUT_02/Q21: IC32.15 (Q4), IC36.6 (A4)
/PULSE_OUT_02/Q22: IC32.14 (Q5), IC36.7 (A5)
/PULSE_OUT_02/Q23: IC32.13 (Q6), IC36.8 (A6)
/PULSE_OUT_02/Q24: IC32.12 (Q7), IC36.9 (A7)
/PULSE_OUT_02/Q25: IC33.19 (Q0), IC37.2 (A0)
/PULSE_OUT_02/Q26: IC33.18 (Q1), IC37.3 (A1)
/PULSE_OUT_02/Q27: IC33.17 (Q2), IC37.4 (A2)
/PULSE_OUT_02/Q28: IC33.16 (Q3), IC37.5 (A3)
/PULSE_OUT_02/Q29: IC33.15 (Q4), IC37.6 (A4)
/PULSE_OUT_02/Q30: IC33.14 (Q5), IC37.7 (A5)
/PULSE_OUT_02/Q31: IC33.13 (Q6), IC37.8 (A6)
/PULSE_OUT_02/Q32: IC33.12 (Q7), IC37.9 (A7)
/PULSE_OUT_02/Q49: IC34.19 (Q0), IC38.2 (A0)
/PULSE_OUT_02/Q50: IC34.18 (Q1), IC38.3 (A1)
/PULSE_OUT_02/Q51: IC34.17 (Q2), IC38.4 (A2)
/PULSE_OUT_02/Q52: IC34.16 (Q3), IC38.5 (A3)
/PULSE_OUT_02/Q53: IC34.15 (Q4), IC38.6 (A4)
/PULSE_OUT_02/Q54: IC34.14 (Q5), IC38.7 (A5)
/PULSE_OUT_02/Q55: IC34.13 (Q6), IC38.8 (A6)
/PULSE_OUT_02/Q56: IC34.12 (Q7), IC38.9 (A7)
/PULSE_OUT_02/Q57: IC35.19 (Q0), IC39.2 (A0)
/PULSE_OUT_02/Q58: IC35.18 (Q1), IC39.3 (A1)
/PULSE_OUT_02/Q59: IC35.17 (Q2), IC39.4 (A2)
/PULSE_OUT_02/Q60: IC35.16 (Q3), IC39.5 (A3)
/PULSE_OUT_02/Q61: IC35.15 (Q4), IC39.6 (A4)
/PULSE_OUT_02/Q62: IC35.14 (Q5), IC39.7 (A5)
/PULSE_OUT_02/Q63: IC35.13 (Q6), IC39.8 (A6)
/PULSE_OUT_02/Q64: IC35.12 (Q7), IC39.9 (A7)
/W01: IC32.11 (Cp), IC33.11 (Cp); also elsewhere on the board
/W03: IC34.11 (Cp), IC35.11 (Cp); also elsewhere on the board
GND: C33.2, C34.2, C35.2, C36.2, C37.2, C38.2, C39.2, C40.2, CN8.2, CN8.4, CN8.6, CN8.8, CN8.10, CN8.12, CN8.14, CN8.16, CN9.2, CN9.4, CN9.6, CN9.8, CN9.10, CN9.12, CN9.14, CN9.16, CN10.2, CN10.4, CN10.6, CN10.8, CN10.10, CN10.12, CN10.14, CN10.16, CN11.2, CN11.4, CN11.6, CN11.8, CN11.10, CN11.12, CN11.14, CN11.16, CN16.2, CN17.2, CN18.2, CN19.2, IC32.1 (OE), IC32.10 (GND), IC33.1 (OE), IC33.10 (GND), IC34.1 (OE), IC34.10 (GND), IC35.1 (OE), IC35.10 (GND), IC36.1 (G1), IC36.10 (GND), IC36.19 (G2), IC37.1 (G1), IC37.10 (GND), IC37.19 (G2), IC38.1 (G1), IC38.10 (GND), IC38.19 (G2), IC39.1 (G1), IC39.10 (GND), IC39.19 (G2); also elsewhere on the board
unnamed: CN8.1, R34.2
unnamed: CN8.3, R35.2
unnamed: CN8.5, R36.2
unnamed: CN8.7, R37.2
unnamed: CN8.9, R38.2
unnamed: CN8.11, R39.2
unnamed: CN8.13, R40.2
unnamed: CN8.15, R41.2
unnamed: CN9.1, R42.2
unnamed: CN9.3, R43.2
unnamed: CN9.5, R44.2
unnamed: CN9.7, R45.2
unnamed: CN9.9, R46.2
unnamed: CN9.11, R47.2
unnamed: CN9.13, R48.2
unnamed: CN9.15, R49.2
unnamed: CN10.1, R50.2
unnamed: CN10.3, R51.2
unnamed: CN10.5, R52.2
unnamed: CN10.7, R53.2
unnamed: CN10.9, R54.2
unnamed: CN10.11, R55.2
unnamed: CN10.13, R56.2
unnamed: CN10.15, R57.2
unnamed: CN11.1, R58.2
unnamed: CN11.3, R59.2
unnamed: CN11.5, R60.2
unnamed: CN11.7, R61.2
unnamed: CN11.9, R62.2
unnamed: CN11.11, R63.2
unnamed: CN11.13, R64.2
unnamed: CN11.15, R65.2

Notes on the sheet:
OUT49
GND
OUT50
OUT51
OUT52
OUT53
OUT54
OUT55
OUT56
OUT57
OUT58
OUT59
OUT60
OUT61
OUT62
OUT63
OUT64
OUT17
OUT18
OUT19
OUT20
OUT21
OUT22
OUT23
OUT24
OUT25
OUT26
OUT27
OUT28
OUT29
OUT30
OUT31
OUT32
+5V
